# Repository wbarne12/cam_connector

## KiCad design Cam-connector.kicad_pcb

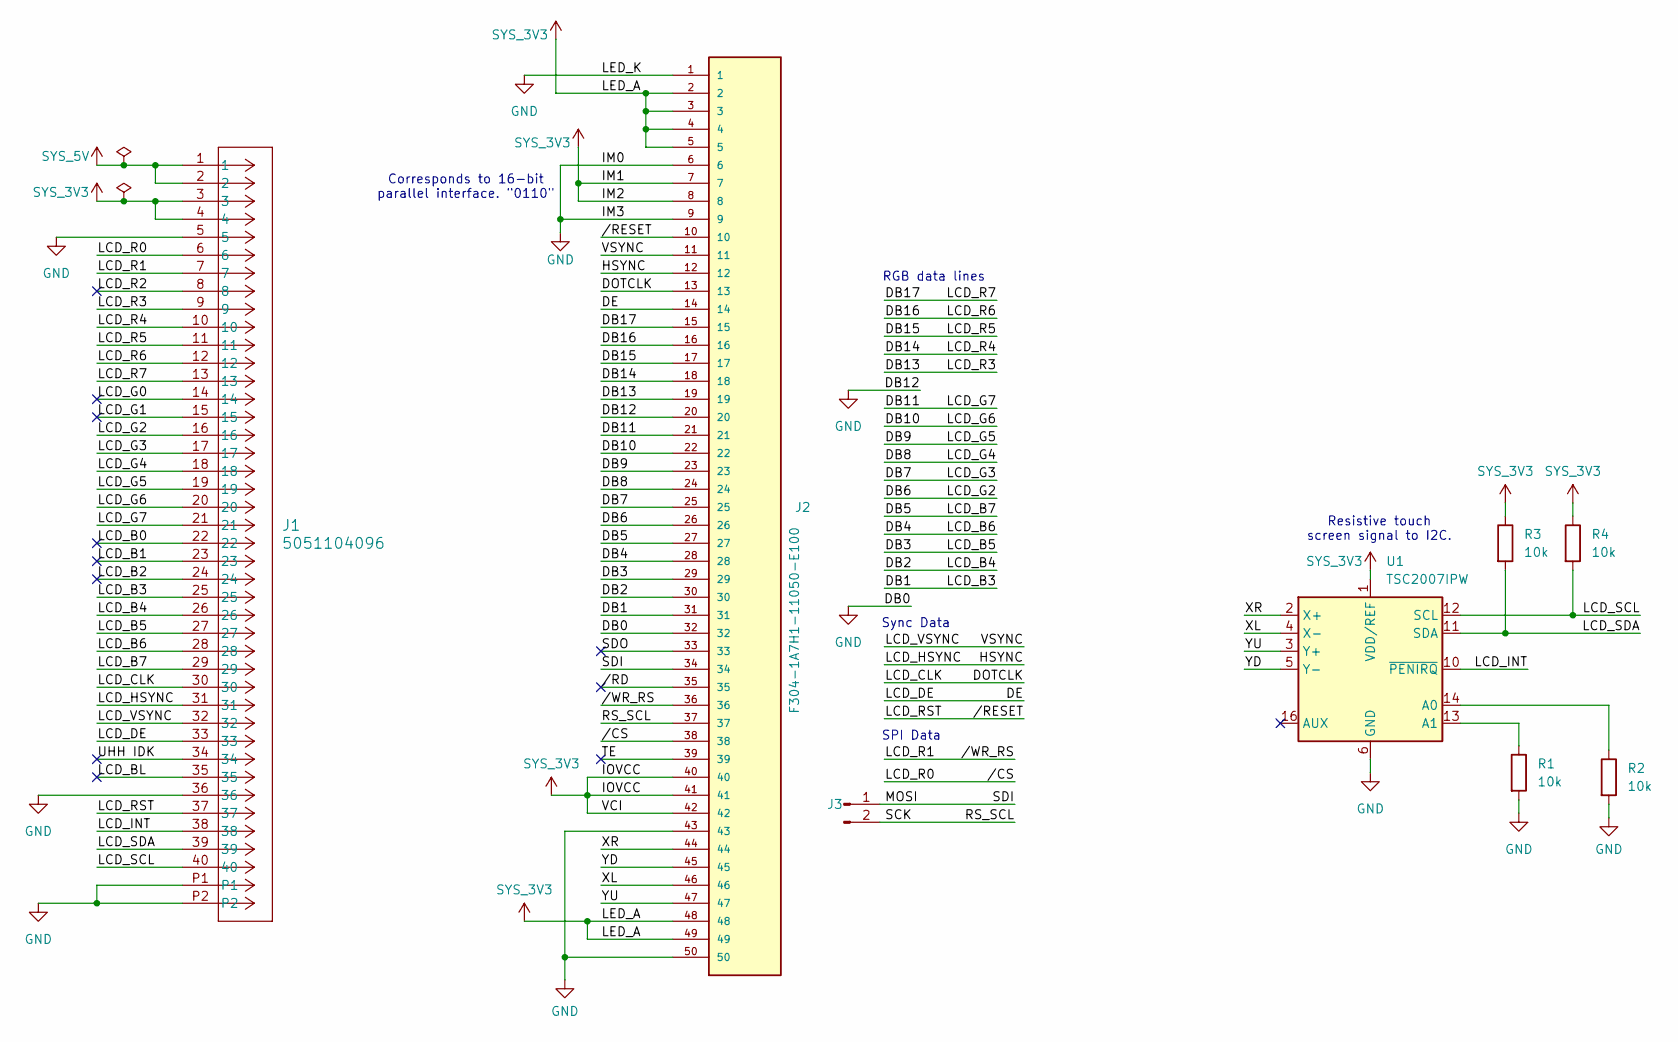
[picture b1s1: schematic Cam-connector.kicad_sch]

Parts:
J1: 5051104096; Hirose_FH12-40S-0.5SH_1x40-1MP_P0.50mm_Horizontal
J2: F304-1A7H1-11050-E100; Hirose_FH12-50S-0.5SH_1x50-1MP_P0.50mm_Horizontal; PARTREV C
J3: Conn_01x02_Pin; PinHeader_1x02_P2.54mm_Vertical
R1, R2, R3, R4: 10k; R_0603_1608Metric
U1: TSC2007IPW; TSSOP-16_4.4x5mm_P0.65mm

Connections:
/DB1: J1.25, J2.31
/DB2: J1.26, J2.30
/DB3: J1.27, J2.29
/DB4: J1.28, J2.28
/DB5: J1.29, J2.27
/DB6: J1.16, J2.26
/DB7: J1.17, J2.25
/DB8: J1.18, J2.24
/DB9: J1.19, J2.23
/DB10: J1.20, J2.22
/DB11: J1.21, J2.21
/DB13: J1.9, J2.19
/DB14: J1.10, J2.18
/DB15: J1.11, J2.17
/DB16: J1.12, J2.16
/DB17: J1.13, J2.15
/DE: J1.33, J2.14
/DOTCLK: J1.30, J2.13
/HSYNC: J1.31, J2.12
/LCD_B0: J1.22
/LCD_B1: J1.23
/LCD_B2: J1.24
/LCD_BL: J1.35
/LCD_G0: J1.14
/LCD_G1: J1.15
/LCD_INT: J1.38, U1.10 (~PENIRQ)
/LCD_R0: J1.6, J2.38
/LCD_R1: J1.7, J2.36
/LCD_R2: J1.8
/LCD_RST: J1.37, J2.10
/LCD_SCL: J1.40, R4.2, U1.12 (SCL)
/LCD_SDA: J1.39, R3.2, U1.11 (SDA)
/LCD_VSYNC: J1.32, J2.11
/MOSI: J2.34, J3.1
/RS_SCL: J2.37, J3.2
/SDO: J2.33
/TE: J2.39
/UHH IDK: J1.34
/XL: J2.46, U1.4 (X-)
/XR: J2.44, U1.2 (X+)
/YD: J2.45, U1.5 (Y-)
/YU: J2.47, U1.3 (Y+)
//RD: J2.35
GND: J1.5, J1.36, J1.P1, J1.P2, J2.1, J2.6, J2.9, J2.20, J2.32, J2.43, J2.50, R1.2, R2.2, U1.6 (GND)
unnamed: R2.1, U1.14 (A0)
unnamed: R1.1, U1.13 (A1)
SYS_3V3: J1.3, J1.4, J2.2, J2.3, J2.4, J2.5, J2.7, J2.8, J2.40, J2.41, J2.42, J2.48, J2.49, R3.1, R4.1, U1.1 (VDD/REF)
SYS_5V: J1.1, J1.2

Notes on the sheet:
Sync Data
SPI Data
Resistive touch screen signal to I2C.
RGB data lines
Corresponds to 16-bit parallel interface. "0110"

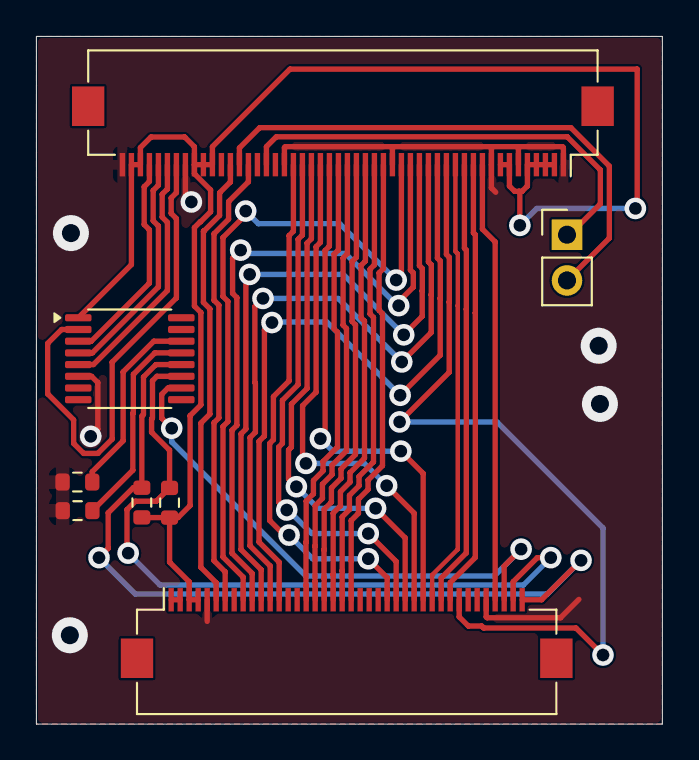
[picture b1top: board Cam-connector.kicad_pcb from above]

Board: 2 copper layers, 34.8 x 38.2 mm, 8 parts (0 on the bottom side), 37 nets.

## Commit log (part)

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2026-06-15 Small form factor
2026-06-15 Voltera printable board
